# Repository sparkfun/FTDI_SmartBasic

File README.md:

FTDI_SmartBasic
===============
[  
*FTDI SmartBasic (DEV-12935)*](https://www.sparkfun.com/products/12935)

The FTDI SmartBasic uses a multiplexer to allow you to multiplex multiple serial 
devices into the hardware port on your Arduino Pro, Pro Mini, or other compatible 
board while still allowing you to program the board via the bootloader.

Repository Contents
-------------------
* **/Hardware** - All Eagle design files (.brd, .sch)
* **/Arduino** - All Arduino board examples
* **/Fritizing** - Fritzing part files
* **/Production** - Test bed files and production panel files

License Information
-------------------
The hardware is released under [Creative Commons Share-alike 3.0](http://creativecommons.org/licenses/by-sa/3.0/).  
All other code is open source so please feel free to do anything you want with it; yo

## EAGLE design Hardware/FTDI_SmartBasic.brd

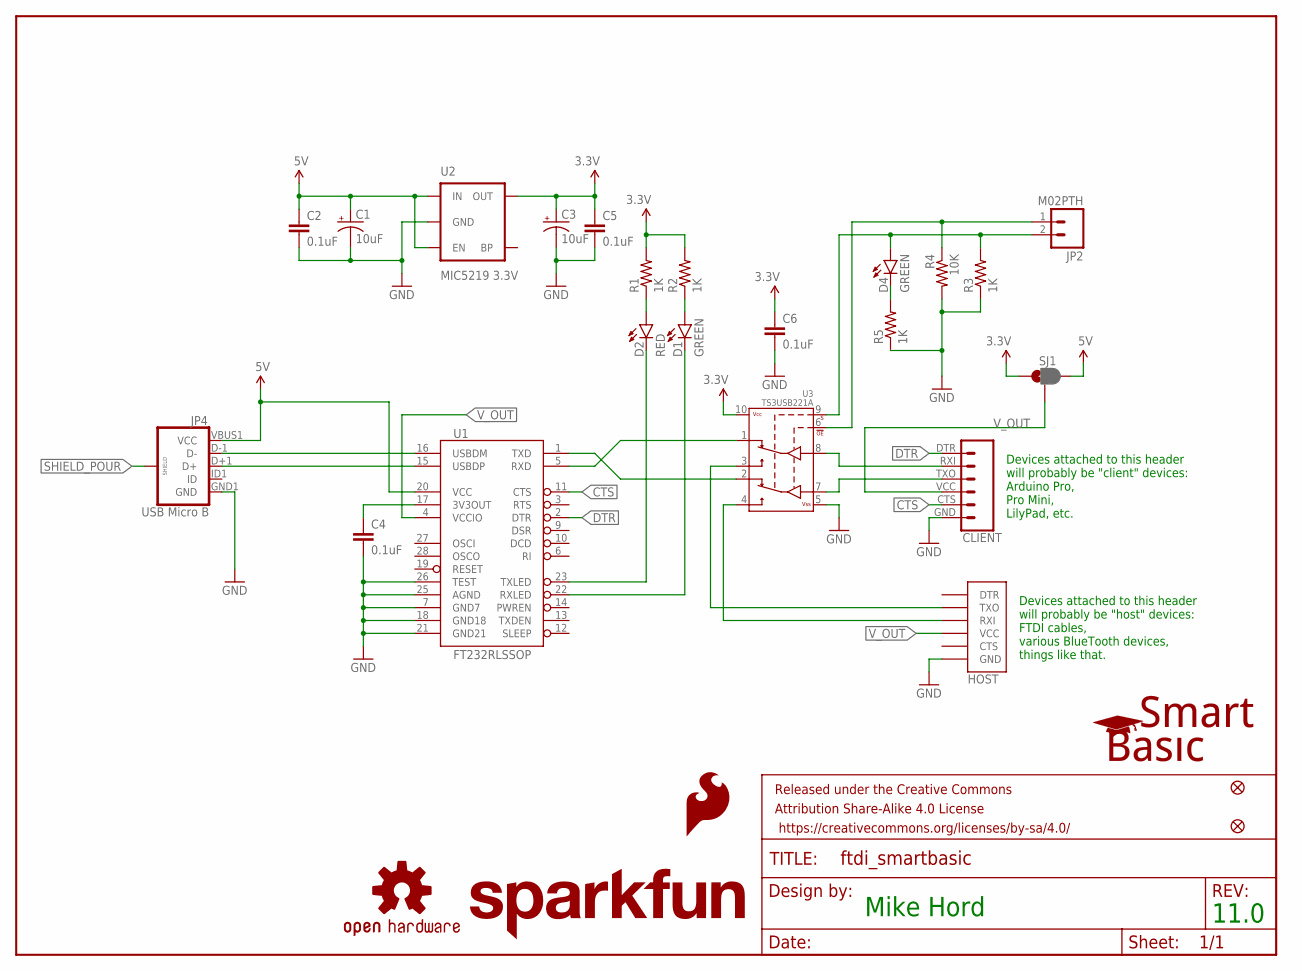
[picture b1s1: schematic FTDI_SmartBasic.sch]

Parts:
C1, C3: 10uF; EIA3216
C2, C4, C5, C6: 0.1uF; 0603-CAP
CLIENT: FTDI_BASICPTH; FTDI_BASIC
D1, D4: GREEN; LED-0603
D2: RED; LED-0603
FID1, FID2: FIDUCIAL1X2; FIDUCIAL-1X2
FRAME1: FRAME-LETTER; CREATIVE_COMMONS
HOST: FTDI_DEVICE; FTDI_DEVICE_SIDE
JP2: M02PTH; 1X02
JP4: USB Micro B; USB-B-MICRO-SMD_V03
LOGO1: SFE_LOGO_NAME.1_INCH; SFE_LOGO_NAME_.1
LOGO2: SFE_LOGO_FLAME.2_INCH; SFE_LOGO_FLAME_.2
LOGO3: OSHW-LOGOS; OSHW-LOGO-S
R1, R2, R3, R5: 1K; 0603-RES
R4: 10K; 0603-RES
SJ1: JUMPER-PAD-3-2OF3_NC_BY_PASTE; PAD-JUMPER-3-2OF3_NC_BY_PASTE_YES_SILK_FULL_BOX
U1: FT232RLSSOP; SSOP28DB
U2: MIC5219 3.3V; SOT23-5
U3: TS3USB221A; QFN-10-RSE
U$1: SMART_BASIC_LOGO

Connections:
3.3V: C3.A (+), C5.1, C6.1, R1.2, R2.2, SJ1.1, U2.5 (OUT), U3.10 (VCC)
5V: C1.A (+), C2.1, JP4.VBUS1 (VCC), SJ1.3, U1.20 (VCC), U2.1 (IN), U2.3 (EN)
!OE: JP2.1, R4.1, U3.6 (!OE)
CTS: CLIENT.CTS (5), U1.11 (CTS)
DTR: CLIENT.DTR (1), U1.2 (DTR)
GND: C1.C (-), C2.2, C3.C (-), C4.2, C5.2, C6.2, CLIENT.GND (6), HOST.P$6 (GND), JP4.GND1 (GND), R3.1, R4.2, R5.1, U1.7 (GND7), U1.18 (GND18), U1.21 (GND21), U1.25 (AGND), U1.26 (TEST), U2.2 (GND), U3.5 (VSS)
unnamed: JP4.D-1 (D-), U1.16 (USBDM)
unnamed: C4.1, U1.17 (3V3OUT)
unnamed: JP4.D+1 (D+), U1.15 (USBDP)
unnamed: D4.C, R5.2
unnamed: D2.A, R1.1
unnamed: D1.A, R2.1
unnamed: U1.5 (RXD), U3.1 (1D+)
unnamed: U1.1 (TXD), U3.2 (1D-)
unnamed: CLIENT.RXI (2), U3.8 (D+)
unnamed: CLIENT.TXO (3), U3.7 (D-)
unnamed: HOST.P$2 (TXO), U3.3 (2D+)
unnamed: HOST.P$3 (RXI), U3.4 (2D-)
RXLED: D1.C, U1.22 (RXLED)
SELECT: D4.A, JP2.2, R3.2, U3.9 (S)
SHIELD_POUR: JP4.SHIELD1 (SHIELD), JP4.SHIELD2 (SHIELD), JP4.SHIELD3 (SHIELD)
TXLED: D2.C, U1.23 (TXLED)
V_OUT: CLIENT.VCC (4), HOST.P$4 (VCC), SJ1.2, U1.4 (VCCIO)

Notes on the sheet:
Devices attached to this header will probably be "host" devices: FTDI cables, various BlueTooth devices, things like that.
Devices attached to this header will probably be "client" devices: Arduino Pro, Pro Mini, LilyPad, etc.
Mike Hord
11.0

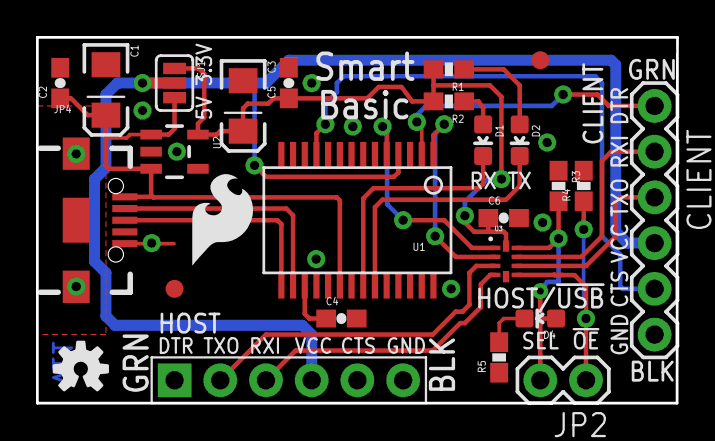
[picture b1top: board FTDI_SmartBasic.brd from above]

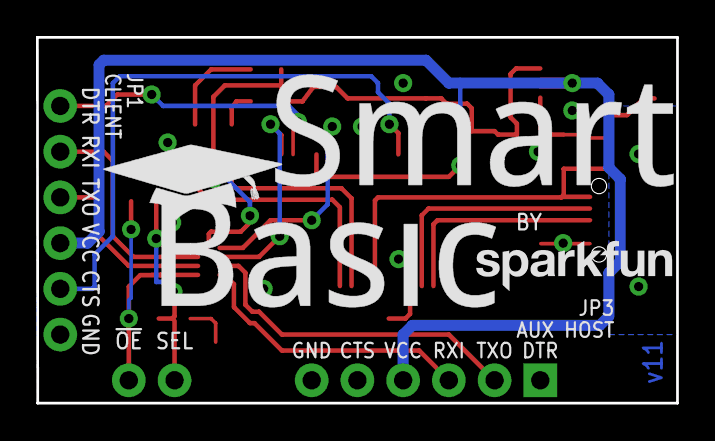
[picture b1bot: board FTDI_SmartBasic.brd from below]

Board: 2 copper layers, 35.6 x 20.3 mm, 29 parts (2 on the bottom side), 23 nets.

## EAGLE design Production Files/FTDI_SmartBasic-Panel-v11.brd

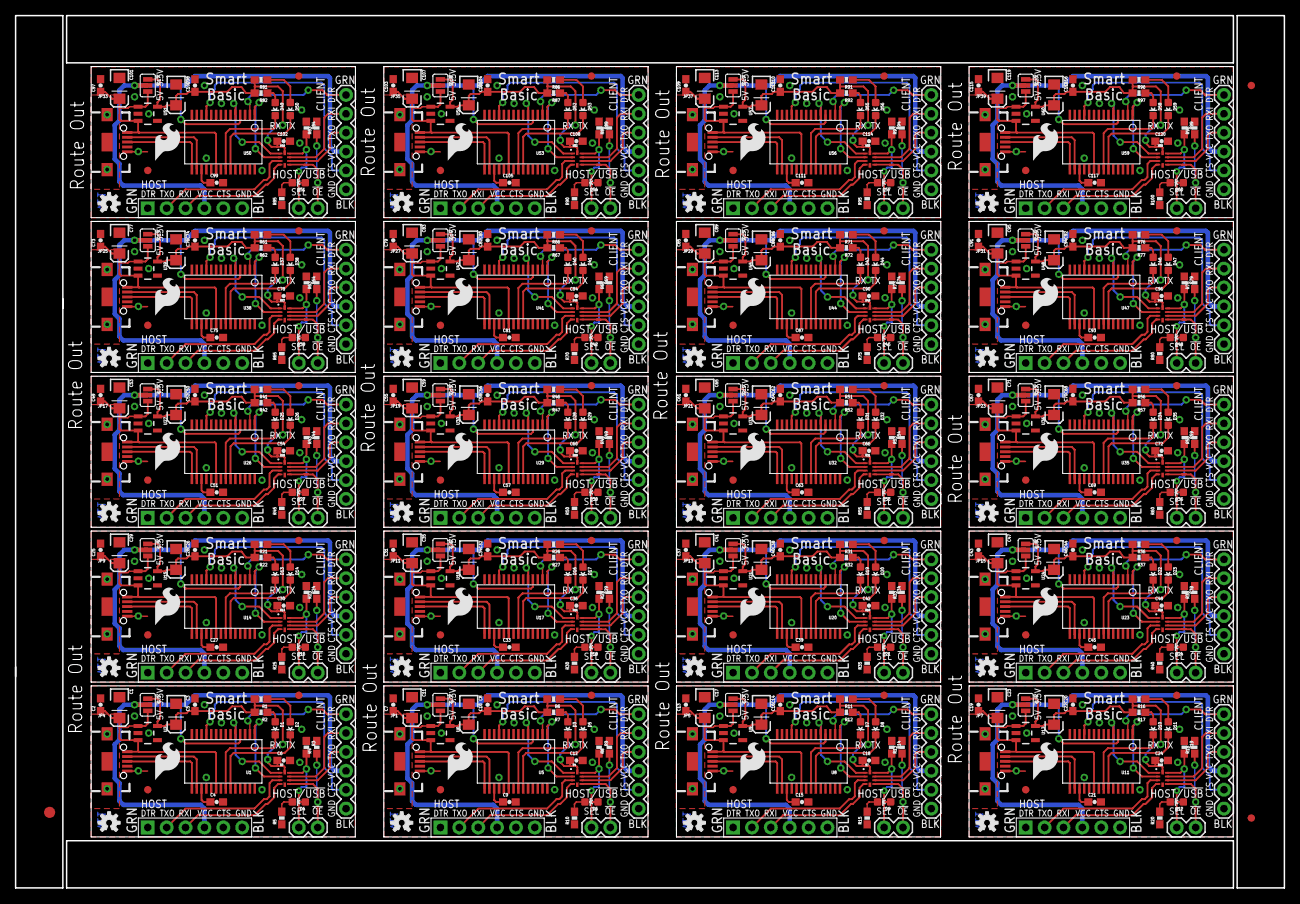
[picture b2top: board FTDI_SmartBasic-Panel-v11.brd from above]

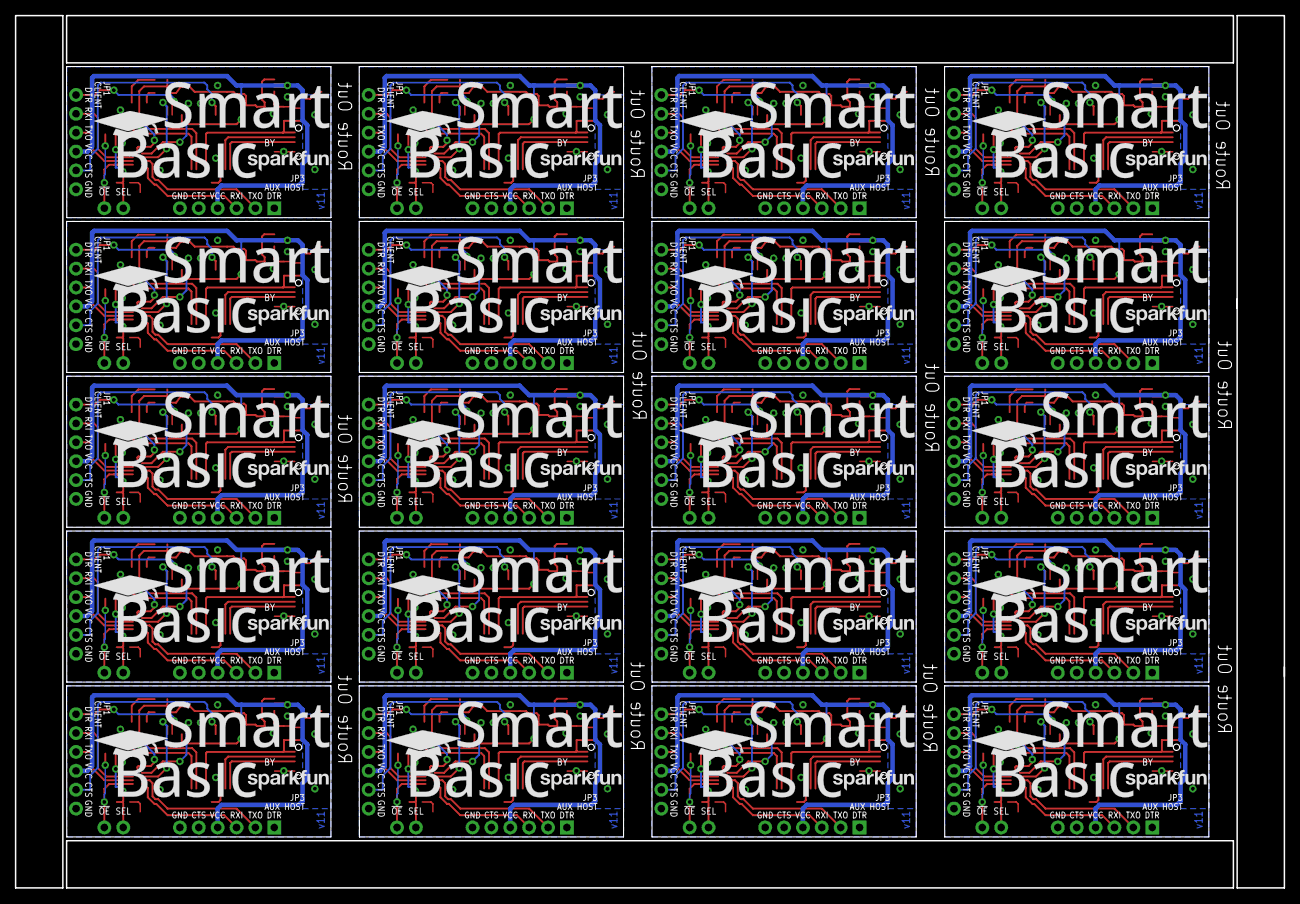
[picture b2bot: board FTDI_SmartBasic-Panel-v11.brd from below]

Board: 2 copper layers, 170.7 x 117.3 mm, 563 parts (40 on the bottom side), 460 nets.

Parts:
C1, C3, C8, C11, C14, C17, C20, C23, C26, C29, C32, C35, C38, C41, C44, C47, C50, C53, C56, C59, C62, C65, C68, C71, C74, C77, C80, C83, C86, C89, C92, C95, C98, C101, C104, C107, C110, C113, C116, C119: 10uF; EIA3216
C2, C4, C5, C6, C7, C9, C10, C12, C13, C15, C16, C18, C19, C21, C22, C24, C25, C27, C28, C30, C31, C33, C34, C36, C37, C39, C40, C42, C43, C45, C46, C48, C49, C51, C52, C54, C55, C57, C58, C60, C61, C63, C64, C66, C67, C69, C70, C72, C73, C75, C76, C78, C79, C81, C82, C84, C85, C87, C88, C90, C91, C93, C94, C96, C97, C99, C100, C102, C103, C105, C106, C108, C109, C111, C112, C114, C115, C117, C118, C120: 0.1uF; 0603-CAP
CLIENT, CLIENT1, CLIENT2, CLIENT3, CLIENT4, CLIENT5, CLIENT6, CLIENT7, CLIENT8, CLIENT9, CLIENT10, CLIENT11, CLIENT12, CLIENT13, CLIENT14, CLIENT15, CLIENT16, CLIENT17, CLIENT18, CLIENT19: FTDI_BASIC
D1, D3, D4, D6, D7, D9, D10, D12, D13, D15, D16, D18, D19, D21, D22, D24, D25, D27, D28, D30, D31, D33, D34, D36, D37, D39, D40, D42, D43, D45, D46, D48, D49, D51, D52, D54, D55, D57, D58, D60: GREEN; LED-0603
D2, D5, D8, D11, D14, D17, D20, D23, D26, D29, D32, D35, D38, D41, D44, D47, D50, D53, D56, D59: RED; LED-0603
E$1: FIDUCIAL-1.5X3
E$5, E$7: FIDUCIAL-1X2
FID1, FID2, FID3, FID4, FID5, FID6, FID7, FID8, FID9, FID10, FID11, FID12, FID13, FID14, FID15, FID16, FID17, FID18, FID19, FID20, FID21, FID22, FID23, FID24, FID25, FID26, FID27, FID28, FID29, FID30, FID31, FID32, FID33, FID34, FID35, FID36, FID37, FID38, FID39, FID40: FIDUCIAL1X2; FIDUCIAL-1X2
HOST, HOST1, HOST2, HOST3, HOST4, HOST5, HOST6, HOST7, HOST8, HOST9, HOST10, HOST11, HOST12, HOST13, HOST14, HOST15, HOST16, HOST17, HOST18, HOST19: FTDI_DEVICE_SIDE
JP1, JP4, JP5, JP7, JP9, JP11, JP13, JP15, JP17, JP19, JP21, JP23, JP25, JP27, JP29, JP31, JP33, JP35, JP37, JP39: USB Micro B; USB-B-MICRO-SMD_V03
JP2, JP3, JP6, JP8, JP10, JP12, JP14, JP16, JP18, JP20, JP22, JP24, JP26, JP28, JP30, JP32, JP34, JP36, JP38, JP40: M02PTH; 1X02
LOGO1, LOGO4, LOGO7, LOGO10, LOGO13, LOGO16, LOGO19, LOGO22, LOGO25, LOGO28, LOGO31, LOGO34, LOGO37, LOGO40, LOGO43, LOGO46, LOGO49, LOGO52, LOGO55, LOGO58: SFE_LOGO_NAME.1_INCH; SFE_LOGO_NAME_.1
LOGO2, LOGO6, LOGO9, LOGO12, LOGO15, LOGO18, LOGO21, LOGO24, LOGO27, LOGO30, LOGO33, LOGO36, LOGO39, LOGO42, LOGO45, LOGO48, LOGO51, LOGO54, LOGO57, LOGO60: SFE_LOGO_FLAME.2_INCH; SFE_LOGO_FLAME_.2
LOGO3, LOGO5, LOGO8, LOGO11, LOGO14, LOGO17, LOGO20, LOGO23, LOGO26, LOGO29, LOGO32, LOGO35, LOGO38, LOGO41, LOGO44, LOGO47, LOGO50, LOGO53, LOGO56, LOGO59: OSHW-LOGOS; OSHW-LOGO-S
R1, R2, R3, R5, R6, R7, R9, R10, R11, R12, R14, R15, R16, R17, R19, R20, R21, R22, R24, R25, R26, R27, R29, R30, R31, R32, R34, R35, R36, R37, R39, R40, R41, R42, R44, R45, R46, R47, R49, R50, R51, R52, R54, R55, R56, R57, R59, R60, R61, R62, R64, R65, R66, R67, R69, R70, R71, R72, R74, R75, R76, R77, R79, R80, R81, R82, R84, R85, R86, R87, R89, R90, R91, R92, R94, R95, R96, R97, R99, R100: 1K; 0603-RES
R4, R8, R13, R18, R23, R28, R33, R38, R43, R48, R53, R58, R63, R68, R73, R78, R83, R88, R93, R98: 10K; 0603-RES
SJ1, SJ2, SJ3, SJ4, SJ5, SJ6, SJ7, SJ8, SJ9, SJ10, SJ11, SJ12, SJ13, SJ14, SJ15, SJ16, SJ17, SJ18, SJ19, SJ20: JUMPER-PAD-3-2OF3_NC_BY_PASTE; PAD-JUMPER-3-2OF3_NC_BY_PASTE_YES_SILK_FULL_BOX
U1, U5, U8, U11, U14, U17, U20, U23, U26, U29, U32, U35, U38, U41, U44, U47, U50, U53, U56, U59: FT232RLSSOP; SSOP28DB
U2, U6, U9, U12, U15, U18, U21, U24, U27, U30, U33, U36, U39, U42, U45, U48, U51, U54, U57, U60: MIC5219 3.3V; SOT23-5
U3, U4, U7, U10, U13, U16, U19, U22, U25, U28, U31, U34, U37, U40, U43, U46, U49, U52, U55, U58: TS3USB221A; QFN-10-RSE
U$1, U$2, U$3, U$4, U$5, U$6, U$7, U$8, U$9, U$10, U$11, U$12, U$13, U$14, U$15, U$16, U$17, U$18, U$19, U$20: SMART_BASIC_LOGO

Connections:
3.3V: C3.A, C5.1, C6.1, R1.2, R2.2, SJ1.1, U2.5, U3.10
3.3V1: C8.A, C10.1, C12.1, R6.2, R7.2, SJ2.1, U4.10, U6.5
3.3V2: C14.A, C16.1, C18.1, R11.2, R12.2, SJ3.1, U7.10, U9.5
3.3V3: C20.A, C22.1, C24.1, R16.2, R17.2, SJ4.1, U10.10, U12.5
3.3V4: C26.A, C28.1, C30.1, R21.2, R22.2, SJ5.1, U13.10, U15.5
3.3V5: C32.A, C34.1, C36.1, R26.2, R27.2, SJ6.1, U16.10, U18.5
3.3V6: C38.A, C40.1, C42.1, R31.2, R32.2, SJ7.1, U19.10, U21.5
3.3V7: C44.A, C46.1, C48.1, R36.2, R37.2, SJ8.1, U22.10, U24.5
3.3V8: C50.A, C52.1, C54.1, R41.2, R42.2, SJ9.1, U25.10, U27.5
3.3V9: C56.A, C58.1, C60.1, R46.2, R47.2, SJ10.1, U28.10, U30.5
3.3V10: C62.A, C64.1, C66.1, R51.2, R52.2, SJ11.1, U31.10, U33.5
3.3V11: C68.A, C70.1, C72.1, R56.2, R57.2, SJ12.1, U34.10, U36.5
3.3V12: C74.A, C76.1, C78.1, R61.2, R62.2, SJ13.1, U37.10, U39.5
3.3V13: C80.A, C82.1, C84.1, R66.2, R67.2, SJ14.1, U40.10, U42.5
3.3V14: C86.A, C88.1, C90.1, R71.2, R72.2, SJ15.1, U43.10, U45.5
3.3V15: C92.A, C94.1, C96.1, R76.2, R77.2, SJ16.1, U46.10, U48.5
3.3V16: C98.A, C100.1, C102.1, R81.2, R82.2, SJ17.1, U49.10, U51.5
3.3V17: C104.A, C106.1, C108.1, R86.2, R87.2, SJ18.1, U52.10, U54.5
3.3V18: C110.A, C112.1, C114.1, R91.2, R92.2, SJ19.1, U55.10, U57.5
3.3V19: C116.A, C118.1, C120.1, R96.2, R97.2, SJ20.1, U58.10, U60.5
5V: C1.A, C2.1, JP4.VBUS1, SJ1.3, U1.20, U2.1, U2.3
5V1: C7.1, C11.A, JP1.VBUS1, SJ2.3, U5.20, U6.1, U6.3
5V2: C13.1, C17.A, JP5.VBUS1, SJ3.3, U8.20, U9.1, U9.3
5V3: C19.1, C23.A, JP7.VBUS1, SJ4.3, U11.20, U12.1, U12.3
5V4: C25.1, C29.A, JP9.VBUS1, SJ5.3, U14.20, U15.1, U15.3
5V5: C31.1, C35.A, JP11.VBUS1, SJ6.3, U17.20, U18.1, U18.3
5V6: C37.1, C41.A, JP13.VBUS1, SJ7.3, U20.20, U21.1, U21.3
5V7: C43.1, C47.A, JP15.VBUS1, SJ8.3, U23.20, U24.1, U24.3
5V8: C49.1, C53.A, JP17.VBUS1, SJ9.3, U26.20, U27.1, U27.3
5V9: C55.1, C59.A, JP19.VBUS1, SJ10.3, U29.20, U30.1, U30.3
5V10: C61.1, C65.A, JP21.VBUS1, SJ11.3, U32.20, U33.1, U33.3
5V11: C67.1, C71.A, JP23.VBUS1, SJ12.3, U35.20, U36.1, U36.3
5V12: C73.1, C77.A, JP25.VBUS1, SJ13.3, U38.20, U39.1, U39.3
5V13: C79.1, C83.A, JP27.VBUS1, SJ14.3, U41.20, U42.1, U42.3
5V14: C85.1, C89.A, JP29.VBUS1, SJ15.3, U44.20, U45.1, U45.3
5V15: C91.1, C95.A, JP31.VBUS1, SJ16.3, U47.20, U48.1, U48.3
5V16: C97.1, C101.A, JP33.VBUS1, SJ17.3, U50.20, U51.1, U51.3
5V17: C103.1, C107.A, JP35.VBUS1, SJ18.3, U53.20, U54.1, U54.3
5V18: C109.1, C113.A, JP37.VBUS1, SJ19.3, U56.20, U57.1, U57.3
5V19: C115.1, C119.A, JP39.VBUS1, SJ20.3, U59.20, U60.1, U60.3
!OE: JP2.1, R4.1, U3.6
!OE1: JP3.1, R8.1, U4.6
!OE2: JP6.1, R13.1, U7.6
!OE3: JP8.1, R18.1, U10.6
!OE4: JP10.1, R23.1, U13.6
!OE5: JP12.1, R28.1, U16.6
!OE6: JP14.1, R33.1, U19.6
!OE7: JP16.1, R38.1, U22.6
!OE8: JP18.1, R43.1, U25.6
!OE9: JP20.1, R48.1, U28.6
!OE10: JP22.1, R53.1, U31.6
!OE11: JP24.1, R58.1, U34.6
!OE12: JP26.1, R63.1, U37.6
!OE13: JP28.1, R68.1, U40.6
!OE14: JP30.1, R73.1, U43.6
!OE15: JP32.1, R78.1, U46.6
!OE16: JP34.1, R83.1, U49.6
!OE17: JP36.1, R88.1, U52.6
!OE18: JP38.1, R93.1, U55.6
!OE19: JP40.1, R98.1, U58.6
CTS: CLIENT.CTS, U1.11
CTS1: CLIENT1.CTS, U5.11
CTS2: CLIENT2.CTS, U8.11
CTS3: CLIENT3.CTS, U11.11
CTS4: CLIENT4.CTS, U14.11
CTS5: CLIENT5.CTS, U17.11
CTS6: CLIENT6.CTS, U20.11
CTS7: CLIENT7.CTS, U23.11
CTS8: CLIENT8.CTS, U26.11
CTS9: CLIENT9.CTS, U29.11
CTS10: CLIENT10.CTS, U32.11
CTS11: CLIENT11.CTS, U35.11
CTS12: CLIENT12.CTS, U38.11
CTS13: CLIENT13.CTS, U41.11
CTS14: CLIENT14.CTS, U44.11
CTS15: CLIENT15.CTS, U47.11
CTS16: CLIENT16.CTS, U50.11
CTS17: CLIENT17.CTS, U53.11
CTS18: CLIENT18.CTS, U56.11
CTS19: CLIENT19.CTS, U59.11
DTR: CLIENT.DTR, U1.2
DTR1: CLIENT1.DTR, U5.2
DTR2: CLIENT2.DTR, U8.2
DTR3: CLIENT3.DTR, U11.2
DTR4: CLIENT4.DTR, U14.2
DTR5: CLIENT5.DTR, U17.2
DTR6: CLIENT6.DTR, U20.2
DTR7: CLIENT7.DTR, U23.2
DTR8: CLIENT8.DTR, U26.2
DTR9: CLIENT9.DTR, U29.2
DTR10: CLIENT10.DTR, U32.2
DTR11: CLIENT11.DTR, U35.2
DTR12: CLIENT12.DTR, U38.2
DTR13: CLIENT13.DTR, U41.2
DTR14: CLIENT14.DTR, U44.2
DTR15: CLIENT15.DTR, U47.2
DTR16: CLIENT16.DTR, U50.2
DTR17: CLIENT17.DTR, U53.2
DTR18: CLIENT18.DTR, U56.2
DTR19: CLIENT19.DTR, U59.2
GND: C1.C, C2.2, C3.C, C4.2, C5.2, C6.2, CLIENT.GND, HOST.P$6, JP4.GND1, R3.1, R4.2, R5.1, U1.7, U1.18, U1.21, U1.25, U1.26, U2.2, U3.5
GND1: C7.2, C8.C, C9.2, C10.2, C11.C, C12.2, CLIENT1.GND, HOST1.P$6, JP1.GND1, R8.2, R9.1, R10.1, U4.5, U5.7, U5.18, U5.21, U5.25, U5.26, U6.2
GND2: C13.2, C14.C, C15.2, C16.2, C17.C, C18.2, CLIENT2.GND, HOST2.P$6, JP5.GND1, R13.2, R14.1, R15.1, U7.5, U8.7, U8.18, U8.21, U8.25, U8.26, U9.2
GND3: C19.2, C20.C, C21.2, C22.2, C23.C, C24.2, CLIENT3.GND, HOST3.P$6, JP7.GND1, R18.2, R19.1, R20.1, U10.5, U11.7, U11.18, U11.21, U11.25, U11.26, U12.2
GND4: C25.2, C26.C, C27.2, C28.2, C29.C, C30.2, CLIENT4.GND, HOST4.P$6, JP9.GND1, R23.2, R24.1, R25.1, U13.5, U14.7, U14.18, U14.21, U14.25, U14.26, U15.2
GND5: C31.2, C32.C, C33.2, C34.2, C35.C, C36.2, CLIENT5.GND, HOST5.P$6, JP11.GND1, R28.2, R29.1, R30.1, U16.5, U17.7, U17.18, U17.21, U17.25, U17.26, U18.2
GND6: C37.2, C38.C, C39.2, C40.2, C41.C, C42.2, CLIENT6.GND, HOST6.P$6, JP13.GND1, R33.2, R34.1, R35.1, U19.5, U20.7, U20.18, U20.21, U20.25, U20.26, U21.2
GND7: C43.2, C44.C, C45.2, C46.2, C47.C, C48.2, CLIENT7.GND, HOST7.P$6, JP15.GND1, R38.2, R39.1, R40.1, U22.5, U23.7, U23.18, U23.21, U23.25, U23.26, U24.2
GND8: C49.2, C50.C, C51.2, C52.2, C53.C, C54.2, CLIENT8.GND, HOST8.P$6, JP17.GND1, R43.2, R44.1, R45.1, U25.5, U26.7, U26.18, U26.21, U26.25, U26.26, U27.2
GND9: C55.2, C56.C, C57.2, C58.2, C59.C, C60.2, CLIENT9.GND, HOST9.P$6, JP19.GND1, R48.2, R49.1, R50.1, U28.5, U29.7, U29.18, U29.21, U29.25, U29.26, U30.2
GND10: C61.2, C62.C, C63.2, C64.2, C65.C, C66.2, CLIENT10.GND, HOST10.P$6, JP21.GND1, R53.2, R54.1, R55.1, U31.5, U32.7, U32.18, U32.21, U32.25, U32.26, U33.2
GND11: C67.2, C68.C, C69.2, C70.2, C71.C, C72.2, CLIENT11.GND, HOST11.P$6, JP23.GND1, R58.2, R59.1, R60.1, U34.5, U35.7, U35.18, U35.21, U35.25, U35.26, U36.2
GND12: C73.2, C74.C, C75.2, C76.2, C77.C, C78.2, CLIENT12.GND, HOST12.P$6, JP25.GND1, R63.2, R64.1, R65.1, U37.5, U38.7, U38.18, U38.21, U38.25, U38.26, U39.2
GND13: C79.2, C80.C, C81.2, C82.2, C83.C, C84.2, CLIENT13.GND, HOST13.P$6, JP27.GND1, R68.2, R69.1, R70.1, U40.5, U41.7, U41.18, U41.21, U41.25, U41.26, U42.2
GND14: C85.2, C86.C, C87.2, C88.2, C89.C, C90.2, CLIENT14.GND, HOST14.P$6, JP29.GND1, R73.2, R74.1, R75.1, U43.5, U44.7, U44.18, U44.21, U44.25, U44.26, U45.2
GND15: C91.2, C92.C, C93.2, C94.2, C95.C, C96.2, CLIENT15.GND, HOST15.P$6, JP31.GND1, R78.2, R79.1, R80.1, U46.5, U47.7, U47.18, U47.21, U47.25, U47.26, U48.2
GND16: C97.2, C98.C, C99.2, C100.2, C101.C, C102.2, CLIENT16.GND, HOST16.P$6, JP33.GND1, R83.2, R84.1, R85.1, U49.5, U50.7, U50.18, U50.21, U50.25, U50.26, U51.2
GND17: C103.2, C104.C, C105.2, C106.2, C107.C, C108.2, CLIENT17.GND, HOST17.P$6, JP35.GND1, R88.2, R89.1, R90.1, U52.5, U53.7, U53.18, U53.21, U53.25, U53.26, U54.2
GND18: C109.2, C110.C, C111.2, C112.2, C113.C, C114.2, CLIENT18.GND, HOST18.P$6, JP37.GND1, R93.2, R94.1, R95.1, U55.5, U56.7, U56.18, U56.21, U56.25, U56.26, U57.2
GND19: C115.2, C116.C, C117.2, C118.2, C119.C, C120.2, CLIENT19.GND, HOST19.P$6, JP39.GND1, R98.2, R99.1, R100.1, U58.5, U59.7, U59.18, U59.21, U59.25, U59.26, U60.2
unnamed: JP4.D-1, U1.16
unnamed: C4.1, U1.17
unnamed: JP4.D+1, U1.15
unnamed: D4.C, R5.2
unnamed: D2.A, R1.1
unnamed: D1.A, R2.1
unnamed: JP1.D-1, U5.16
unnamed: JP1.D+1, U5.15
unnamed: D5.A, R6.1
unnamed: D3.A, R7.1
unnamed: U1.5, U3.1
unnamed: U1.1, U3.2
unnamed: CLIENT.RXI, U3.8
unnamed: CLIENT.TXO, U3.7
unnamed: CLIENT1.RXI, U4.8
unnamed: HOST.P$2, U3.3
unnamed: HOST.P$3, U3.4
unnamed: CLIENT1.TXO, U4.7
unnamed: U4.1, U5.5
unnamed: U4.2, U5.1
unnamed: HOST1.P$2, U4.3
unnamed: HOST1.P$3, U4.4
unnamed: C9.1, U5.17
unnamed: D6.C, R10.2
unnamed: JP5.D-1, U8.16
unnamed: JP5.D+1, U8.15
unnamed: D8.A, R11.1
unnamed: D7.A, R12.1
unnamed: CLIENT2.RXI, U7.8
unnamed: CLIENT2.TXO, U7.7
unnamed: U7.1, U8.5
unnamed: U7.2, U8.1
unnamed: HOST2.P$2, U7.3
unnamed: HOST2.P$3, U7.4
unnamed: C15.1, U8.17
unnamed: D9.C, R15.2
unnamed: JP7.D-1, U11.16
unnamed: JP7.D+1, U11.15
unnamed: D11.A, R16.1
unnamed: D10.A, R17.1
unnamed: CLIENT3.RXI, U10.8
unnamed: CLIENT3.TXO, U10.7
unnamed: U10.1, U11.5
unnamed: U10.2, U11.1
unnamed: HOST3.P$2, U10.3
unnamed: HOST3.P$3, U10.4
unnamed: C21.1, U11.17
unnamed: D12.C, R20.2
unnamed: JP9.D-1, U14.16
unnamed: JP9.D+1, U14.15
unnamed: D14.A, R21.1
unnamed: D13.A, R22.1
unnamed: CLIENT4.RXI, U13.8
unnamed: CLIENT4.TXO, U13.7
unnamed: U13.1, U14.5
unnamed: U13.2, U14.1
unnamed: HOST4.P$2, U13.3
unnamed: HOST4.P$3, U13.4
unnamed: C27.1, U14.17
unnamed: D15.C, R25.2
unnamed: JP11.D-1, U17.16
unnamed: JP11.D+1, U17.15
unnamed: D17.A, R26.1
unnamed: D16.A, R27.1
unnamed: CLIENT5.RXI, U16.8
unnamed: CLIENT5.TXO, U16.7
unnamed: U16.1, U17.5
unnamed: U16.2, U17.1
unnamed: HOST5.P$2, U16.3
unnamed: HOST5.P$3, U16.4
unnamed: C33.1, U17.17
unnamed: D18.C, R30.2
unnamed: JP13.D-1, U20.16
unnamed: JP13.D+1, U20.15
unnamed: D20.A, R31.1
unnamed: D19.A, R32.1
unnamed: CLIENT6.RXI, U19.8
unnamed: CLIENT6.TXO, U19.7
unnamed: U19.1, U20.5
unnamed: U19.2, U20.1
unnamed: HOST6.P$2, U19.3
unnamed: HOST6.P$3, U19.4
unnamed: C39.1, U20.17
unnamed: D21.C, R35.2
unnamed: JP15.D-1, U23.16
unnamed: JP15.D+1, U23.15
unnamed: D23.A, R36.1
unnamed: D22.A, R37.1
unnamed: CLIENT7.RXI, U22.8
unnamed: CLIENT7.TXO, U22.7
unnamed: U22.1, U23.5
unnamed: U22.2, U23.1
unnamed: HOST7.P$2, U22.3
unnamed: HOST7.P$3, U22.4
unnamed: C45.1, U23.17
unnamed: D24.C, R40.2
unnamed: JP17.D-1, U26.16
unnamed: JP17.D+1, U26.15
unnamed: D26.A, R41.1
unnamed: D25.A, R42.1
unnamed: CLIENT8.RXI, U25.8
unnamed: CLIENT8.TXO, U25.7
unnamed: U25.1, U26.5
unnamed: U25.2, U26.1
unnamed: HOST8.P$2, U25.3
unnamed: HOST8.P$3, U25.4
unnamed: C51.1, U26.17
unnamed: D27.C, R45.2
unnamed: JP19.D-1, U29.16
unnamed: JP19.D+1, U29.15
unnamed: D29.A, R46.1
unnamed: D28.A, R47.1
unnamed: CLIENT9.RXI, U28.8
unnamed: CLIENT9.TXO, U28.7
unnamed: U28.1, U29.5
unnamed: U28.2, U29.1
unnamed: HOST9.P$2, U28.3
unnamed: HOST9.P$3, U28.4
unnamed: C57.1, U29.17
unnamed: D30.C, R50.2
unnamed: JP21.D-1, U32.16
unnamed: JP21.D+1, U32.15
unnamed: D32.A, R51.1
unnamed: D31.A, R52.1
unnamed: CLIENT10.RXI, U31.8
unnamed: CLIENT10.TXO, U31.7
unnamed: U31.1, U32.5
unnamed: U31.2, U32.1
unnamed: HOST10.P$2, U31.3
unnamed: HOST10.P$3, U31.4
unnamed: C63.1, U32.17
unnamed: D33.C, R55.2
unnamed: JP23.D-1, U35.16
unnamed: JP23.D+1, U35.15
unnamed: D35.A, R56.1
unnamed: D34.A, R57.1
unnamed: CLIENT11.RXI, U34.8
unnamed: CLIENT11.TXO, U34.7
unnamed: U34.1, U35.5
unnamed: U34.2, U35.1
unnamed: HOST11.P$2, U34.3
unnamed: HOST11.P$3, U34.4
unnamed: C69.1, U35.17
unnamed: D36.C, R60.2
unnamed: JP25.D-1, U38.16
unnamed: JP25.D+1, U38.15
unnamed: D38.A, R61.1
unnamed: D37.A, R62.1
unnamed: CLIENT12.RXI, U37.8
unnamed: CLIENT12.TXO, U37.7
unnamed: U37.1, U38.5
unnamed: U37.2, U38.1
unnamed: HOST12.P$2, U37.3
unnamed: HOST12.P$3, U37.4
unnamed: C75.1, U38.17
unnamed: D39.C, R65.2
unnamed: JP27.D-1, U41.16
unnamed: JP27.D+1, U41.15
unnamed: D41.A, R66.1
unnamed: D40.A, R67.1
unnamed: CLIENT13.RXI, U40.8
unnamed: CLIENT13.TXO, U40.7
unnamed: U40.1, U41.5
unnamed: U40.2, U41.1
unnamed: HOST13.P$2, U40.3
unnamed: HOST13.P$3, U40.4
unnamed: C81.1, U41.17
unnamed: D42.C, R70.2
unnamed: JP29.D-1, U44.16
unnamed: JP29.D+1, U44.15
unnamed: D44.A, R71.1
unnamed: D43.A, R72.1
unnamed: CLIENT14.RXI, U43.8
unnamed: CLIENT14.TXO, U43.7
unnamed: U43.1, U44.5
unnamed: U43.2, U44.1
unnamed: HOST14.P$2, U43.3
unnamed: HOST14.P$3, U43.4
unnamed: C87.1, U44.17
unnamed: D45.C, R75.2
unnamed: JP31.D-1, U47.16
unnamed: JP31.D+1, U47.15
unnamed: D47.A, R76.1
unnamed: D46.A, R77.1
unnamed: CLIENT15.RXI, U46.8
unnamed: CLIENT15.TXO, U46.7
unnamed: U46.1, U47.5
unnamed: U46.2, U47.1
unnamed: HOST15.P$2, U46.3
unnamed: HOST15.P$3, U46.4
unnamed: C93.1, U47.17
unnamed: D48.C, R80.2
unnamed: JP33.D-1, U50.16
unnamed: JP33.D+1, U50.15
unnamed: D50.A, R81.1
unnamed: D49.A, R82.1
unnamed: CLIENT16.RXI, U49.8
unnamed: CLIENT16.TXO, U49.7
unnamed: U49.1, U50.5
unnamed: U49.2, U50.1
unnamed: HOST16.P$2, U49.3
unnamed: HOST16.P$3, U49.4
unnamed: C99.1, U50.17
unnamed: D51.C, R85.2
unnamed: JP35.D-1, U53.16
unnamed: JP35.D+1, U53.15
unnamed: D53.A, R86.1
unnamed: D52.A, R87.1
unnamed: CLIENT17.RXI, U52.8
unnamed: CLIENT17.TXO, U52.7
unnamed: U52.1, U53.5
unnamed: U52.2, U53.1
unnamed: HOST17.P$2, U52.3
unnamed: HOST17.P$3, U52.4
unnamed: C105.1, U53.17
unnamed: D54.C, R90.2
unnamed: JP37.D-1, U56.16
unnamed: JP37.D+1, U56.15
unnamed: D56.A, R91.1
unnamed: D55.A, R92.1
unnamed: CLIENT18.RXI, U55.8
unnamed: CLIENT18.TXO, U55.7
unnamed: U55.1, U56.5
unnamed: U55.2, U56.1
unnamed: HOST18.P$2, U55.3
unnamed: HOST18.P$3, U55.4
unnamed: C111.1, U56.17
unnamed: D57.C, R95.2
unnamed: JP39.D-1, U59.16
unnamed: JP39.D+1, U59.15
unnamed: D59.A, R96.1
unnamed: D58.A, R97.1
unnamed: CLIENT19.RXI, U58.8
unnamed: CLIENT19.TXO, U58.7
unnamed: U58.1, U59.5
unnamed: U58.2, U59.1
unnamed: HOST19.P$2, U58.3
unnamed: HOST19.P$3, U58.4
unnamed: C117.1, U59.17
unnamed: D60.C, R100.2
RXLED: D1.C, U1.22
RXLED1: D3.C, U5.22
RXLED2: D7.C, U8.22
RXLED3: D10.C, U11.22
RXLED4: D13.C, U14.22
RXLED5: D16.C, U17.22
RXLED6: D19.C, U20.22
RXLED7: D22.C, U23.22
RXLED8: D25.C, U26.22
RXLED9: D28.C, U29.22
RXLED10: D31.C, U32.22
RXLED11: D34.C, U35.22
RXLED12: D37.C, U38.22
RXLED13: D40.C, U41.22
RXLED14: D43.C, U44.22
RXLED15: D46.C, U47.22
RXLED16: D49.C, U50.22
RXLED17: D52.C, U53.22
RXLED18: D55.C, U56.22
RXLED19: D58.C, U59.22
SELECT: D4.A, JP2.2, R3.2, U3.9
SELECT1: D6.A, JP3.2, R9.2, U4.9
SELECT2: D9.A, JP6.2, R14.2, U7.9
SELECT3: D12.A, JP8.2, R19.2, U10.9
SELECT4: D15.A, JP10.2, R24.2, U13.9
SELECT5: D18.A, JP12.2, R29.2, U16.9
SELECT6: D21.A, JP14.2, R34.2, U19.9
SELECT7: D24.A, JP16.2, R39.2, U22.9
SELECT8: D27.A, JP18.2, R44.2, U25.9
SELECT9: D30.A, JP20.2, R49.2, U28.9
SELECT10: D33.A, JP22.2, R54.2, U31.9
SELECT11: D36.A, JP24.2, R59.2, U34.9
SELECT12: D39.A, JP26.2, R64.2, U37.9
SELECT13: D42.A, JP28.2, R69.2, U40.9
SELECT14: D45.A, JP30.2, R74.2, U43.9
SELECT15: D48.A, JP32.2, R79.2, U46.9
SELECT16: D51.A, JP34.2, R84.2, U49.9
SELECT17: D54.A, JP36.2, R89.2, U52.9
SELECT18: D57.A, JP38.2, R94.2, U55.9
SELECT19: D60.A, JP40.2, R99.2, U58.9
SHIELD_POUR: JP4.SHIELD1, JP4.SHIELD2, JP4.SHIELD3
SHIELD_POUR1: JP1.SHIELD1, JP1.SHIELD2, JP1.SHIELD3
SHIELD_POUR2: JP5.SHIELD1, JP5.SHIELD2, JP5.SHIELD3
SHIELD_POUR3: JP7.SHIELD1, JP7.SHIELD2, JP7.SHIELD3
SHIELD_POUR4: JP9.SHIELD1, JP9.SHIELD2, JP9.SHIELD3
SHIELD_POUR5: JP11.SHIELD1, JP11.SHIELD2, JP11.SHIELD3
SHIELD_POUR6: JP13.SHIELD1, JP13.SHIELD2, JP13.SHIELD3
SHIELD_POUR7: JP15.SHIELD1, JP15.SHIELD2, JP15.SHIELD3
SHIELD_POUR8: JP17.SHIELD1, JP17.SHIELD2, JP17.SHIELD3
SHIELD_POUR9: JP19.SHIELD1, JP19.SHIELD2, JP19.SHIELD3
SHIELD_POUR10: JP21.SHIELD1, JP21.SHIELD2, JP21.SHIELD3
SHIELD_POUR11: JP23.SHIELD1, JP23.SHIELD2, JP23.SHIELD3
SHIELD_POUR12: JP25.SHIELD1, JP25.SHIELD2, JP25.SHIELD3
SHIELD_POUR13: JP27.SHIELD1, JP27.SHIELD2, JP27.SHIELD3
SHIELD_POUR14: JP29.SHIELD1, JP29.SHIELD2, JP29.SHIELD3
SHIELD_POUR15: JP31.SHIELD1, JP31.SHIELD2, JP31.SHIELD3
SHIELD_POUR16: JP33.SHIELD1, JP33.SHIELD2, JP33.SHIELD3
SHIELD_POUR17: JP35.SHIELD1, JP35.SHIELD2, JP35.SHIELD3
SHIELD_POUR18: JP37.SHIELD1, JP37.SHIELD2, JP37.SHIELD3
SHIELD_POUR19: JP39.SHIELD1, JP39.SHIELD2, JP39.SHIELD3
TXLED: D2.C, U1.23
TXLED1: D5.C, U5.23
TXLED2: D8.C, U8.23
TXLED3: D11.C, U11.23
TXLED4: D14.C, U14.23
TXLED5: D17.C, U17.23
TXLED6: D20.C, U20.23
TXLED7: D23.C, U23.23
TXLED8: D26.C, U26.23
TXLED9: D29.C, U29.23
TXLED10: D32.C, U32.23
TXLED11: D35.C, U35.23
TXLED12: D38.C, U38.23
TXLED13: D41.C, U41.23
TXLED14: D44.C, U44.23
TXLED15: D47.C, U47.23
TXLED16: D50.C, U50.23
TXLED17: D53.C, U53.23
TXLED18: D56.C, U56.23
TXLED19: D59.C, U59.23
V_OUT: CLIENT.VCC, HOST.P$4, SJ1.2, U1.4
V_OUT1: CLIENT1.VCC, HOST1.P$4, SJ2.2, U5.4
V_OUT2: CLIENT2.VCC, HOST2.P$4, SJ3.2, U8.4
V_OUT3: CLIENT3.VCC, HOST3.P$4, SJ4.2, U11.4
V_OUT4: CLIENT4.VCC, HOST4.P$4, SJ5.2, U14.4
V_OUT5: CLIENT5.VCC, HOST5.P$4, SJ6.2, U17.4
V_OUT6: CLIENT6.VCC, HOST6.P$4, SJ7.2, U20.4
V_OUT7: CLIENT7.VCC, HOST7.P$4, SJ8.2, U23.4
V_OUT8: CLIENT8.VCC, HOST8.P$4, SJ9.2, U26.4
V_OUT9: CLIENT9.VCC, HOST9.P$4, SJ10.2, U29.4
V_OUT10: CLIENT10.VCC, HOST10.P$4, SJ11.2, U32.4
V_OUT11: CLIENT11.VCC, HOST11.P$4, SJ12.2, U35.4
V_OUT12: CLIENT12.VCC, HOST12.P$4, SJ13.2, U38.4
V_OUT13: CLIENT13.VCC, HOST13.P$4, SJ14.2, U41.4
V_OUT14: CLIENT14.VCC, HOST14.P$4, SJ15.2, U44.4
V_OUT15: CLIENT15.VCC, HOST15.P$4, SJ16.2, U47.4
V_OUT16: CLIENT16.VCC, HOST16.P$4, SJ17.2, U50.4
V_OUT17: CLIENT17.VCC, HOST17.P$4, SJ18.2, U53.4
V_OUT18: CLIENT18.VCC, HOST18.P$4, SJ19.2, U56.4
V_OUT19: CLIENT19.VCC, HOST19.P$4, SJ20.2, U59.4

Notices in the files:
parts and their libraries:
SparkFun-Aesthetics: Licensing: Creative Commons ShareAlike 4.0 International - https://creativecommons.org/licenses/by-sa/4.0
SparkFun-Aesthetics: Released under the Creative Commons Attribution Share-Alike 4.0 License
SparkFun-Aesthetics: https://creativecommons.org/licenses/by-sa/4.0
